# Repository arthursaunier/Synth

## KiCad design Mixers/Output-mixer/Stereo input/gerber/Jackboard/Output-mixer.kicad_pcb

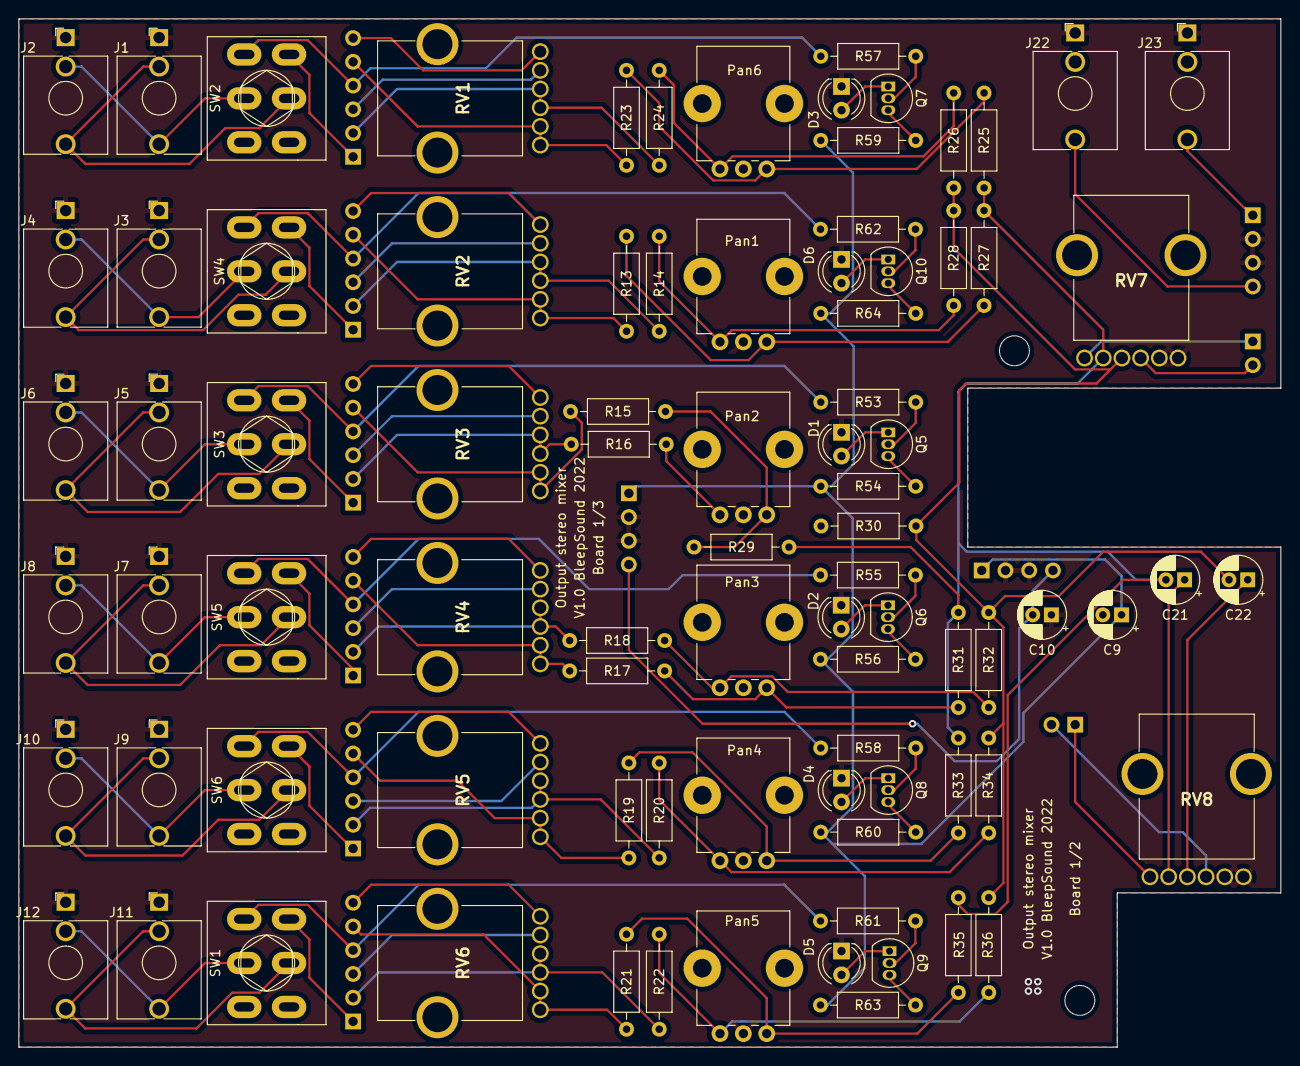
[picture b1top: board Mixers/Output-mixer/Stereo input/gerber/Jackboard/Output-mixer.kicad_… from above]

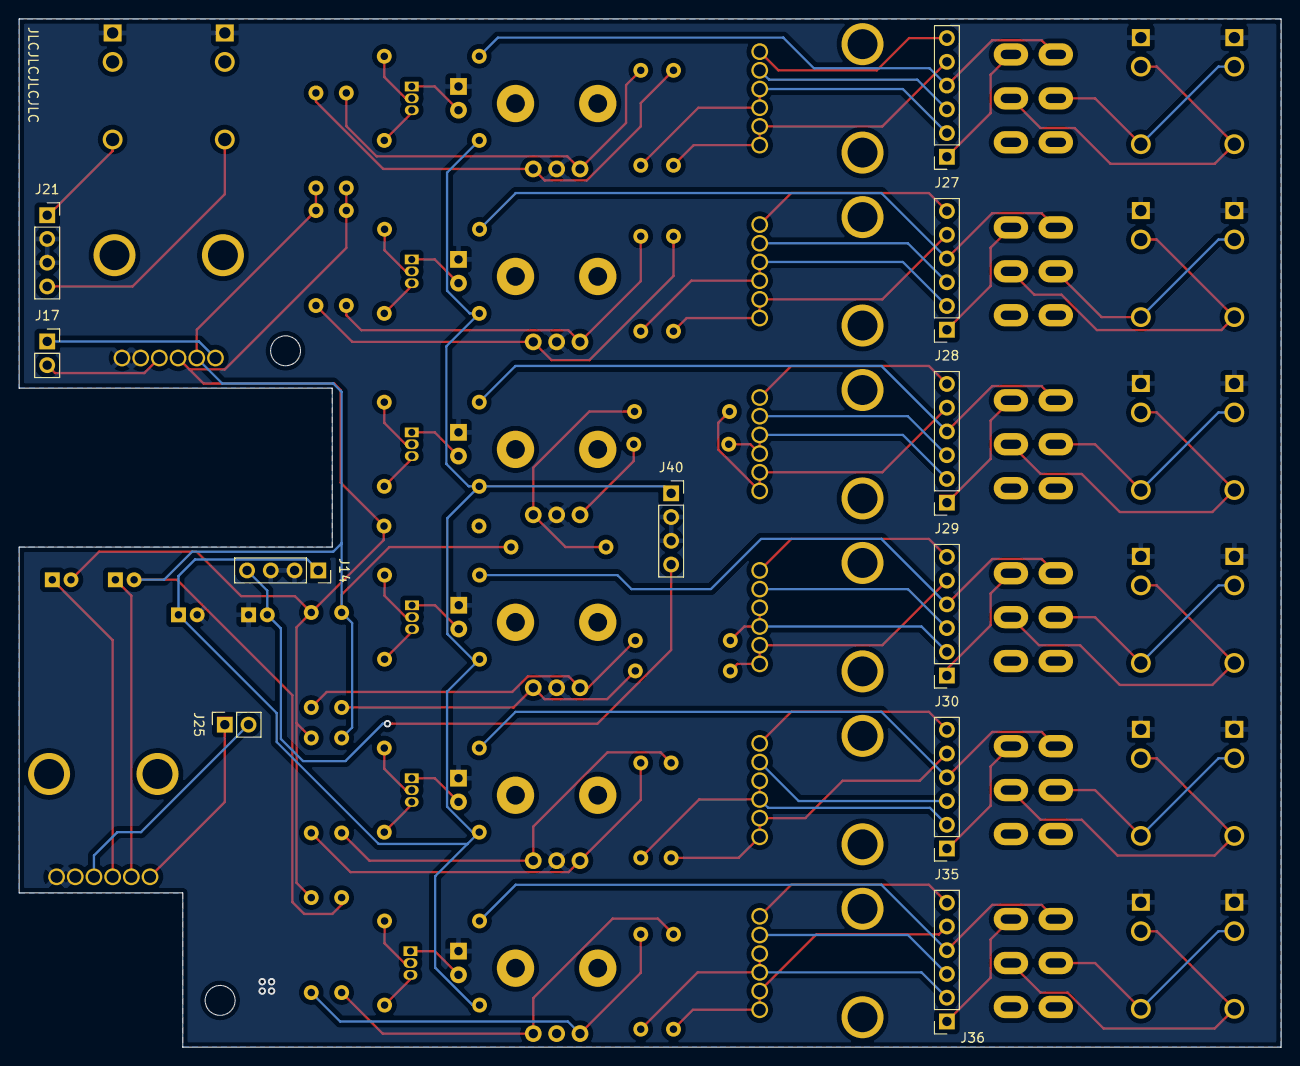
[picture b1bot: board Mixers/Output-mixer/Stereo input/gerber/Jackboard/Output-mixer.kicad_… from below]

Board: 2 copper layers, 135.0 x 110.0 mm, 99 parts (11 on the bottom side), 91 nets.

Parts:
C9, C10: 10µ; CP_Radial_D5.0mm_P2.00mm
C21, C22: 1µF; CP_Radial_D5.0mm_P2.00mm
D1, D2, D3, D4, D5, D6: Signal; LED_D4.0mm
H5, H7: SpacerHoles; MountingHole_3.2mm_M3
J1, J2, J3, J4, J5, J6, J7, J8, J9, J10, J11, J12: In; Thonkiconn
J14, J40: Conn_01x04_Female; PinSocket_1x04_P2.54mm_Vertical
J17, J25: Conn_01x02_Female; PinSocket_1x02_P2.54mm_Vertical
J21: Jack 3.5 Out; PinSocket_1x04_P2.54mm_Vertical
J22: OutL; Thonkiconn
J23: OutR; Thonkiconn
J27, J28, J29, J30, J35, J36: Conn_01x06_Female; PinSocket_1x06_P2.54mm_Vertical
Pan1, Pan2, Pan3, Pan4, Pan5, Pan6: 50k; Pot-bourns-alpha
Q5, Q6, Q7, Q8, Q9, Q10: 2N3904; TO-92_Inline
R13, R14, R15, R16, R17, R18, R19, R20, R21, R22, R23, R24: 2k2; R_Axial_DIN0207_L6.3mm_D2.5mm_P10.16mm_Horizontal
R25, R26, R27, R28, R29, R30, R31, R32, R33, R34, R35, R36: 47k; R_Axial_DIN0207_L6.3mm_D2.5mm_P10.16mm_Horizontal
R53, R55, R57, R58, R61, R62: 100k; R_Axial_DIN0207_L6.3mm_D2.5mm_P10.16mm_Horizontal
R54, R56, R59, R60, R63, R64: 1k; R_Axial_DIN0207_L6.3mm_D2.5mm_P10.16mm_Horizontal
RV1, RV2, RV3, RV4, RV5, RV6, RV7, RV8: 50k; PTV1124420AA503
SW1, SW2, SW3, SW4, SW5, SW6: Mute; SW_DPDT_Toggle

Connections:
+12V: C9.1, J14.1, J40.1, R54.1, R56.1, R59.1, R60.1, R63.1, R64.1
-12V: C10.2, J14.4, J40.4
/AmpL: J17.1, RV7.2
/AmpR: J17.2, RV7.5
/Headphones Amp/HeadAmpL: J25.1, RV8.2
/Headphones Amp/HeadAmpR: J25.2, RV8.5
/OutL: J21.4, J22.T
/OutR: J21.1, J23.T
GND: C9.2, C10.1, D1.1 (K), D2.1 (K), D3.1 (K), D4.1 (K), D5.1 (K), D6.1 (K), J1.S, J2.S, J3.S, J4.S, J5.S, J6.S, J7.S, J8.S, J9.S, J10.S, J11.S, J12.S, J14.2, J14.3, J21.2, J21.3, J22.S, J23.S, J40.2, J40.3, Pan1.2, Pan2.2, Pan3.2, Pan4.2, Pan5.2, Pan6.2, RV7.3, RV7.6, RV8.3, RV8.6
L: C21.2, R25.2, R27.2, R29.2, R31.2, R33.2, R35.2, RV7.1
Left1_GOut: J27.3, RV1.6
Left1_In: J27.1, SW2.4 (A)
Left1_Out: J27.2, R24.2, RV1.4, RV1.5
Left2_GOut: J28.3, RV2.6
Left2_In: J28.1, SW4.4 (A)
Left2_Out: J28.2, R14.2, RV2.4, RV2.5
Left3_GOut: J29.3, RV3.6
Left3_In: J29.1, SW3.4 (A)
Left3_Out: J29.2, R16.2, RV3.4, RV3.5
Left4_GOut: J30.3, RV4.6
Left4_In: J30.1, SW5.4 (A)
Left4_Out: J30.2, R18.2, RV4.4, RV4.5
Left5_GOut: J35.3, RV5.6
Left5_In: J35.1, SW6.4 (A)
Left5_Out: J35.2, R20.2, RV5.4, RV5.5
Left6_GOut: J36.3, RV6.6
Left6_In: J36.1, SW1.4 (A)
Left6_Out: J36.2, R22.2, RV6.4, RV6.5
unnamed: C21.1, RV8.1
unnamed: C22.1, RV8.4
unnamed: D1.2 (A), Q5.1 (E)
unnamed: D2.2 (A), Q6.1 (E)
unnamed: D3.2 (A), Q7.1 (E)
unnamed: D4.2 (A), Q8.1 (E)
unnamed: D5.2 (A), Q9.1 (E)
unnamed: D6.2 (A), Q10.1 (E)
unnamed: J1.T, J2.TN, SW2.2 (B)
unnamed: J1.TN, J2.T, SW2.5 (B)
unnamed: J3.T, J4.TN, SW4.2 (B)
unnamed: J3.TN, J4.T, SW4.5 (B)
unnamed: J5.T, J6.TN, SW3.2 (B)
unnamed: J5.TN, J6.T, SW3.5 (B)
unnamed: J7.T, J8.TN, SW5.2 (B)
unnamed: J7.TN, J8.T, SW5.5 (B)
unnamed: J9.TN, J10.T, SW6.5 (B)
unnamed: J9.T, J10.TN, SW6.2 (B)
unnamed: J11.T, J12.TN, SW1.2 (B)
unnamed: J11.TN, J12.T, SW1.5 (B)
unnamed: Pan1.1, R13.2, R27.1
unnamed: Pan1.3, R14.1, R28.2
unnamed: Pan2.1, R15.2, R29.1
unnamed: Pan2.3, R16.1, R30.2
unnamed: Pan3.1, R17.2, R31.1
unnamed: Pan3.3, R18.1, R32.2
unnamed: Pan4.1, R19.2, R33.1
unnamed: Pan4.3, R20.1, R34.2
unnamed: Pan5.1, R21.2, R35.1
unnamed: Pan5.3, R22.1, R36.2
unnamed: Pan6.1, R23.2, R25.1
unnamed: Pan6.3, R24.1, R26.2
unnamed: Q5.2 (B), R53.2
unnamed: Q5.3 (C), R54.2
unnamed: Q6.2 (B), R55.2
unnamed: Q6.3 (C), R56.2
unnamed: Q7.2 (B), R57.2
unnamed: Q7.3 (C), R59.2
unnamed: Q8.2 (B), R58.2
unnamed: Q8.3 (C), R60.2
unnamed: Q9.2 (B), R61.2
unnamed: Q9.3 (C), R63.2
unnamed: Q10.2 (B), R62.2
unnamed: Q10.3 (C), R64.2
R: C22.2, R26.1, R28.1, R30.1, R32.1, R34.1, R36.1, RV7.4
Right1_GOut: J27.6, RV1.3
Right1_In: J27.4, R57.1, SW2.1 (A)
Right1_Out: J27.5, R23.1, RV1.1, RV1.2
Right2_GOut: J28.6, RV2.3
Right2_In: J28.4, R62.1, SW4.1 (A)
Right2_Out: J28.5, R13.1, RV2.1, RV2.2
Right3_GOut: J29.6, RV3.3
Right3_In: J29.4, R53.1, SW3.1 (A)
Right3_Out: J29.5, R15.1, RV3.1, RV3.2
Right4_GOut: J30.6, RV4.3
Right4_In: J30.4, R55.1, SW5.1 (A)
Right4_Out: J30.5, R17.1, RV4.1, RV4.2
Right5_GOut: J35.6, RV5.3
Right5_In: J35.4, R58.1, SW6.1 (A)
Right5_Out: J35.5, R19.1, RV5.1, RV5.2
Right6_GOut: J36.6, RV6.3
Right6_In: J36.4, R61.1, SW1.1 (A)
Right6_Out: J36.5, R21.1, RV6.1, RV6.2

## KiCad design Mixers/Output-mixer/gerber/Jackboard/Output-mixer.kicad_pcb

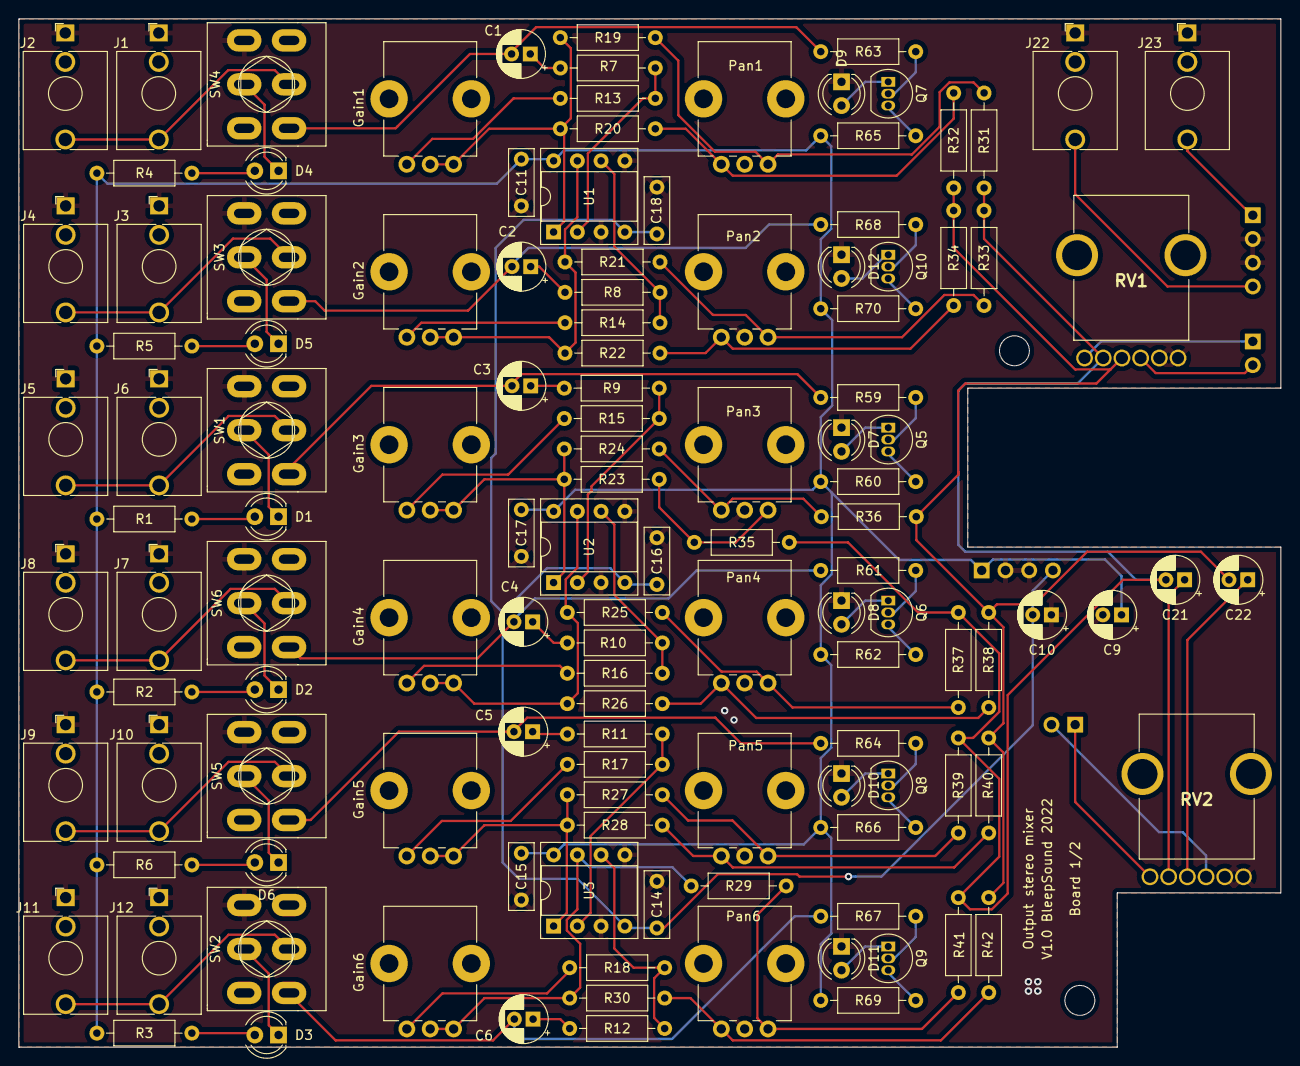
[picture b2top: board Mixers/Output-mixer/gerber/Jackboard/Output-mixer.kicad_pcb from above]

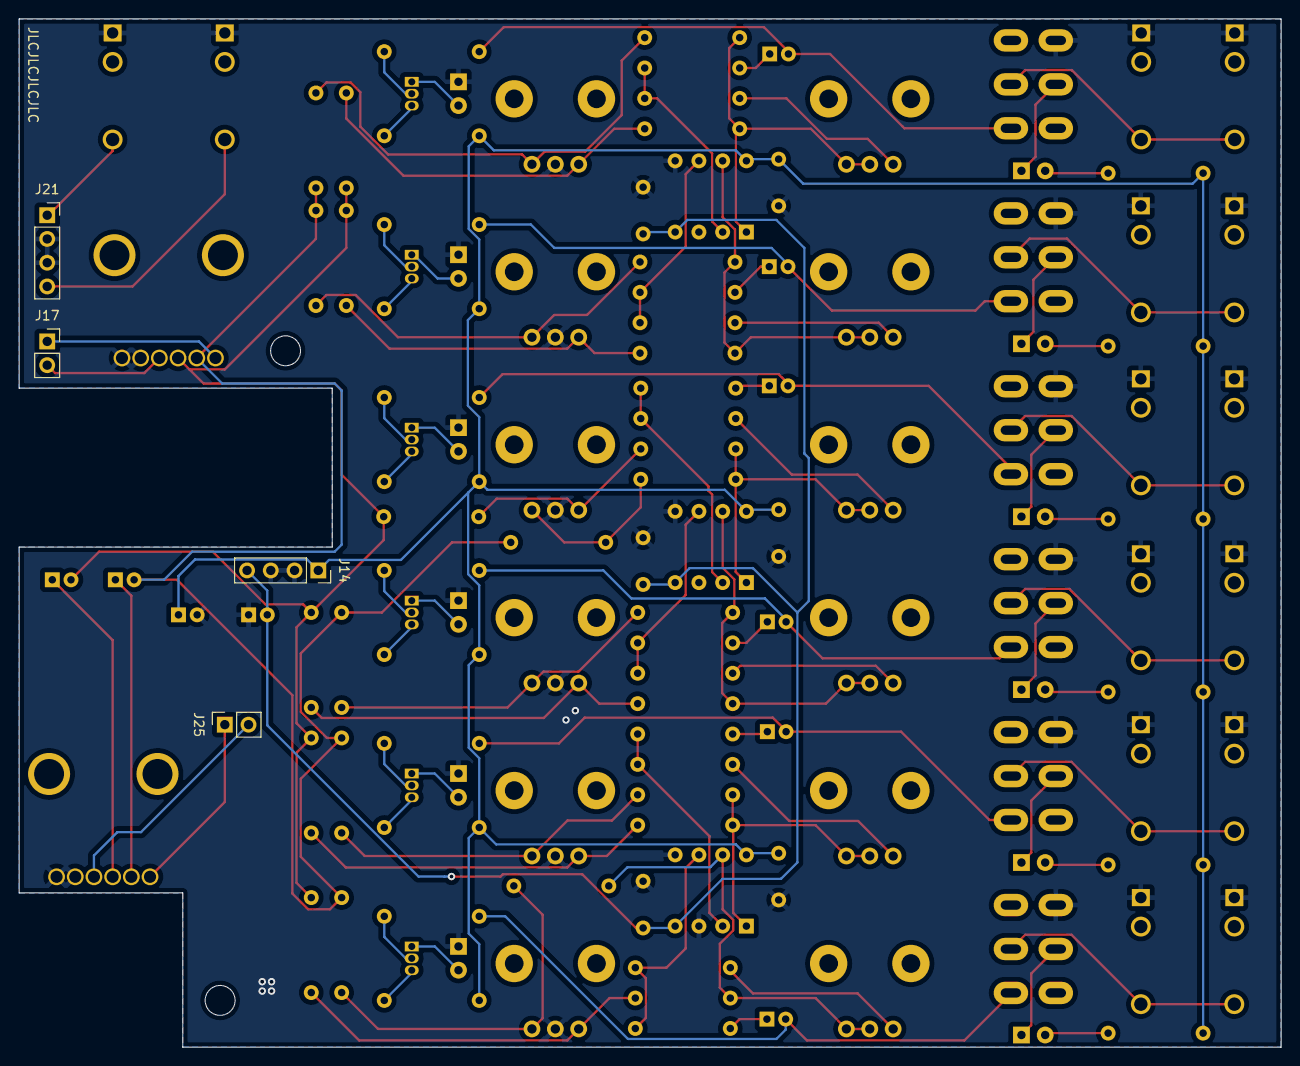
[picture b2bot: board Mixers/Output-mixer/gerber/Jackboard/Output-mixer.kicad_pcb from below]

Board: 2 copper layers, 135.0 x 110.0 mm, 131 parts (4 on the bottom side), 91 nets.

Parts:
C1, C2, C3, C4, C5, C6: .1µF; CP_Radial_D5.0mm_P2.00mm
C9, C10: 10µ; CP_Radial_D5.0mm_P2.00mm
C11, C14, C15, C16, C17, C18: 100nF; C_Disc_D7.0mm_W2.5mm_P5.00mm
C21, C22: 1µF; CP_Radial_D5.0mm_P2.00mm
D1, D2, D3, D4, D5, D6: LED-mute; LED_D4.0mm
D7, D8, D9, D10, D11, D12: Signal; LED_D4.0mm
Gain1, Gain2, Gain3, Gain4, Gain5, Gain6: 500k; Pot-bourns-alpha
H5, H7: SpacerHoles; MountingHole_3.2mm_M3
J1, J2, J3, J4, J5, J6, J7, J8, J9, J10, J11, J12: In; Thonkiconn
J14: Conn_01x04_Female; PinSocket_1x04_P2.54mm_Vertical
J17, J25: Conn_01x02_Female; PinSocket_1x02_P2.54mm_Vertical
J21: Jack 3.5 Out; PinSocket_1x04_P2.54mm_Vertical
J22: OutL; Thonkiconn
J23: OutR; Thonkiconn
Pan1, Pan2, Pan3, Pan4, Pan5, Pan6: 50k; Pot-bourns-alpha
Q5, Q6, Q7, Q8, Q9, Q10: 2N3904; TO-92_Inline
R1, R2, R3, R4, R5, R6: 2.2k; R_Axial_DIN0207_L6.3mm_D2.5mm_P10.16mm_Horizontal
R7, R8, R9, R10, R11, R12, R59, R61, R63, R64, R67, R68: 100k; R_Axial_DIN0207_L6.3mm_D2.5mm_P10.16mm_Horizontal
R13, R14, R15, R16, R17, R18: 10k; R_Axial_DIN0207_L6.3mm_D2.5mm_P10.16mm_Horizontal
R19, R20, R21, R22, R23, R24, R25, R26, R27, R28, R29, R30: 2k2; R_Axial_DIN0207_L6.3mm_D2.5mm_P10.16mm_Horizontal
R31, R32, R33, R34, R35, R36, R37, R38, R39, R40, R41, R42: 47k; R_Axial_DIN0207_L6.3mm_D2.5mm_P10.16mm_Horizontal
R60, R62, R65, R66, R69, R70: 1k; R_Axial_DIN0207_L6.3mm_D2.5mm_P10.16mm_Horizontal
RV1, RV2: 50k; PTV1124420AA503
SW1, SW2, SW3, SW4, SW5, SW6: Mute; SW_DPDT_Toggle
U1, U2, U3: TL072; DIP-8_W7.62mm_Socket

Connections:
+12V: C9.1, C11.1, C15.1, C17.1, J14.1, R1.1, R2.1, R3.1, R4.1, R5.1, R6.1, R60.1, R62.1, R65.1, R66.1, R69.1, R70.1, U1.8 (V+), U2.8 (V+), U3.8 (V+)
-12V: C10.2, C14.2, C16.2, C18.2, J14.4, U1.4 (V-), U2.4 (V-), U3.4 (V-)
/AmpL: J17.1, RV1.2
/AmpR: J17.2, RV1.5
/Headphones Amp/HeadAmpL: J25.1, RV2.2
/Headphones Amp/HeadAmpR: J25.2, RV2.5
/OutL: J21.4, J22.T
/OutR: J21.1, J23.T
GND: C9.2, C10.1, C11.2, C14.1, C15.2, C16.1, C17.2, C18.1, D7.1 (K), D8.1 (K), D9.1 (K), D10.1 (K), D11.1 (K), D12.1 (K), J1.S, J2.S, J3.S, J4.S, J5.S, J6.S, J7.S, J8.S, J9.S, J10.S, J11.S, J12.S, J14.2, J14.3, J21.2, J21.3, J22.S, J23.S, Pan1.2, Pan2.2, Pan3.2, Pan4.2, Pan5.2, Pan6.2, RV1.3, RV1.6, RV2.3, RV2.6, SW1.1 (A), SW2.1 (A), SW3.1 (A), SW4.1 (A), SW5.1 (A), SW6.1 (A), U1.3 (+), U1.5 (+), U2.3 (+), U2.5 (+), U3.3 (+), U3.5 (+)
In1: C1.2, R63.1, SW4.6 (C)
In2: C2.2, R68.1, SW3.6 (C)
In3: C3.2, R59.1, SW1.6 (C)
In4: C4.2, R61.1, SW6.6 (C)
In5: C5.2, R64.1, SW5.6 (C)
In6: C6.2, R67.1, SW2.6 (C)
L: C21.2, R31.2, R33.2, R35.2, R37.2, R39.2, R41.2, RV1.1
unnamed: C1.1, R7.2
unnamed: C2.1, R8.2
unnamed: C3.1, R9.2
unnamed: C4.1, R10.2
unnamed: C5.1, R11.2
unnamed: C6.1, R12.2
unnamed: C21.1, RV2.1
unnamed: C22.1, RV2.4
unnamed: D1.1 (K), SW1.2 (B)
unnamed: D1.2 (A), R1.2
unnamed: D2.1 (K), SW6.2 (B)
unnamed: D2.2 (A), R2.2
unnamed: D3.1 (K), SW2.2 (B)
unnamed: D3.2 (A), R3.2
unnamed: D4.1 (K), SW4.2 (B)
unnamed: D4.2 (A), R4.2
unnamed: D5.1 (K), SW3.2 (B)
unnamed: D5.2 (A), R5.2
unnamed: D6.1 (K), SW5.2 (B)
unnamed: D6.2 (A), R6.2
unnamed: D7.2 (A), Q5.1 (E)
unnamed: D8.2 (A), Q6.1 (E)
unnamed: D9.2 (A), Q7.1 (E)
unnamed: D10.2 (A), Q8.1 (E)
unnamed: D11.2 (A), Q9.1 (E)
unnamed: D12.2 (A), Q10.1 (E)
unnamed: Gain1.1, Gain1.2, R19.1, R20.2, U1.1
unnamed: Gain1.3, R13.1
unnamed: Gain2.1, Gain2.2, R21.1, R22.2, U1.7
unnamed: Gain2.3, R14.1
unnamed: Gain3.1, Gain3.2, R23.1, R24.2, U2.1
unnamed: Gain3.3, R15.1
unnamed: Gain4.1, Gain4.2, R25.1, R26.2, U2.7
unnamed: Gain4.3, R16.1
unnamed: Gain5.1, Gain5.2, R27.1, R28.2, U3.1
unnamed: Gain5.3, R17.1
unnamed: Gain6.1, Gain6.2, R29.1, R30.2, U3.7
unnamed: Gain6.3, R18.1
unnamed: J1.T, J2.T, SW4.5 (B)
unnamed: J3.T, J4.T, SW3.5 (B)
unnamed: J5.T, J6.T, SW1.5 (B)
unnamed: J7.T, J8.T, SW6.5 (B)
unnamed: J9.T, J10.T, SW5.5 (B)
unnamed: J11.T, J12.T, SW2.5 (B)
unnamed: Pan1.1, R19.2, R31.1
unnamed: Pan1.3, R20.1, R32.2
unnamed: Pan2.1, R21.2, R33.1
unnamed: Pan2.3, R22.1, R34.2
unnamed: Pan3.1, R23.2, R35.1
unnamed: Pan3.3, R24.1, R36.2
unnamed: Pan4.1, R25.2, R37.1
unnamed: Pan4.3, R26.1, R38.2
unnamed: Pan5.1, R27.2, R39.1
unnamed: Pan5.3, R28.1, R40.2
unnamed: Pan6.1, R29.2, R41.1
unnamed: Pan6.3, R30.1, R42.2
unnamed: Q5.2 (B), R59.2
unnamed: Q5.3 (C), R60.2
unnamed: Q6.2 (B), R61.2
unnamed: Q6.3 (C), R62.2
unnamed: Q7.2 (B), R63.2
unnamed: Q7.3 (C), R65.2
unnamed: Q8.2 (B), R64.2
unnamed: Q8.3 (C), R66.2
unnamed: Q9.2 (B), R67.2
unnamed: Q9.3 (C), R69.2
unnamed: Q10.2 (B), R68.2
unnamed: Q10.3 (C), R70.2
unnamed: R10.1, R16.2, U2.6 (-)
unnamed: R11.1, R17.2, U3.2 (-)
unnamed: R12.1, R18.2, U3.6 (-)
unnamed: R7.1, R13.2, U1.2 (-)
unnamed: R8.1, R14.2, U1.6 (-)
unnamed: R9.1, R15.2, U2.2 (-)
R: C22.2, R32.1, R34.1, R36.1, R38.1, R40.1, R42.1, RV1.4

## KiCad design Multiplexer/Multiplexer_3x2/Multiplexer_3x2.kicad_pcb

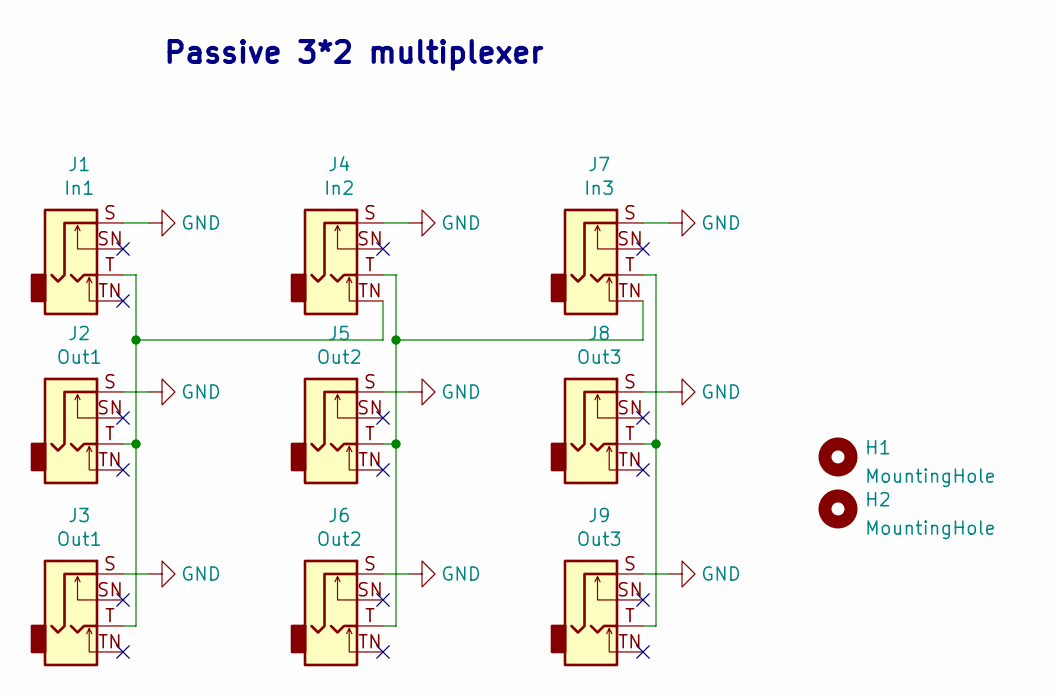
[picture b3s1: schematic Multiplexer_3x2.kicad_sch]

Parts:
H1, H2: MountingHole; Doepfer Mounting hole
J1: In1; Jack_3.5mm_QingPu_WQP-PJ398SM_Vertical_CircularHoles
J2, J3: Out1; Jack_3.5mm_QingPu_WQP-PJ398SM_Vertical_CircularHoles
J4: In2; Jack_3.5mm_QingPu_WQP-PJ398SM_Vertical_CircularHoles
J5, J6: Out2; Jack_3.5mm_QingPu_WQP-PJ398SM_Vertical_CircularHoles
J7: In3; Jack_3.5mm_QingPu_WQP-PJ398SM_Vertical_CircularHoles
J8, J9: Out3; Jack_3.5mm_QingPu_WQP-PJ398SM_Vertical_CircularHoles

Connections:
GND: J1.S, J2.S, J3.S, J4.S, J5.S, J6.S, J7.S, J8.S, J9.S
unnamed: J4.T, J5.T, J6.T, J7.TN
unnamed: J1.T, J2.T, J3.T, J4.TN
unnamed: J7.T, J8.T, J9.T

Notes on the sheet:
Passive 3*2 multiplexer

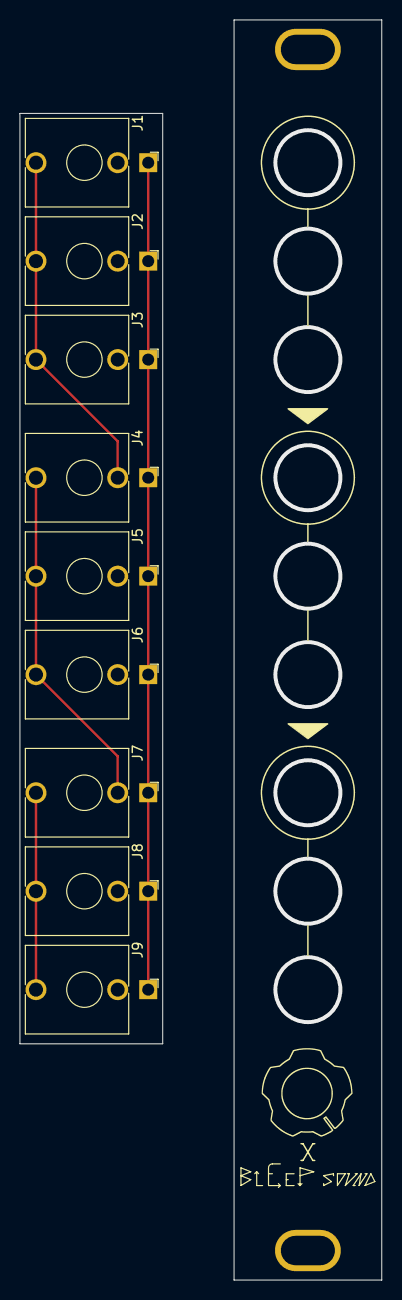
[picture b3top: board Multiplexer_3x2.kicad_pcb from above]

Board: 2 copper layers, 14.5 x 94.5 mm, 11 parts (0 on the bottom side), 4 nets.

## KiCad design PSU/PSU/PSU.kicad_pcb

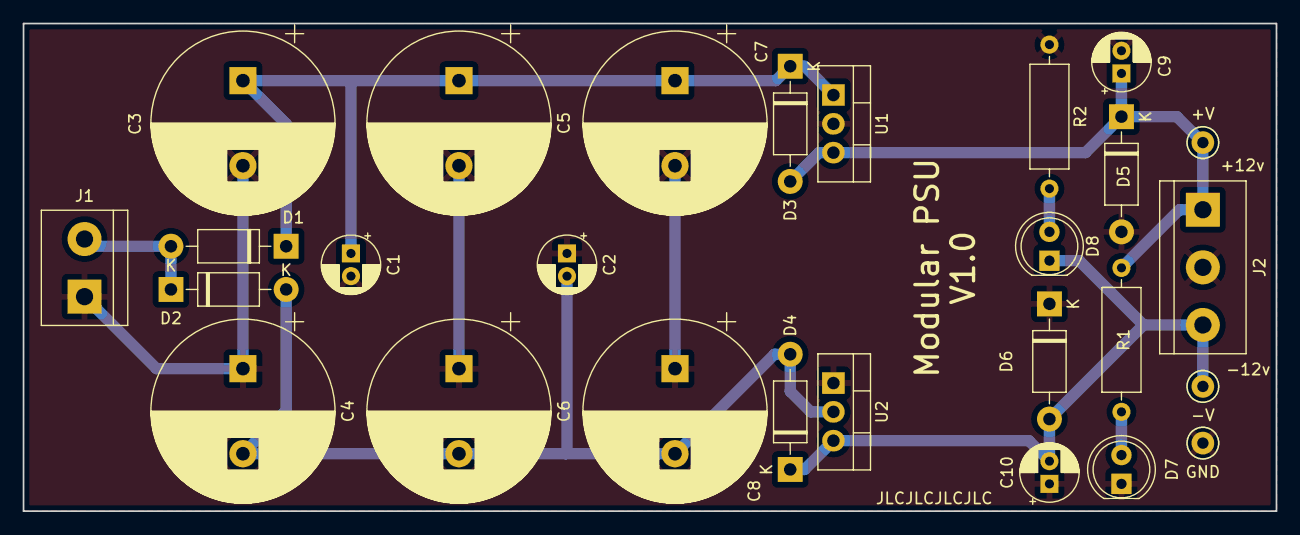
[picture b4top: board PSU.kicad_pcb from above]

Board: 2 copper layers, 110.5 x 43.0 mm, 27 parts (0 on the bottom side), 8 nets.

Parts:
C1, C2: 1µF; CP_Radial_D5.0mm_P2.00mm
C3, C4, C5, C6, C7, C8: 4700µF; CP_Radial_D16.0mm_P7.50mm
C9, C10: 100µF; CP_Radial_D5.0mm_P2.00mm
D1, D2, D3, D4, D5, D6: 1N4004; D_DO-41_SOD81_P10.16mm_Horizontal
D7, D8: LED; LED_D5.0mm_Clear
J1: Power_Input; TerminalBlock_bornier-2_P5.08mm
J2: Screw_Terminal_01x03; TerminalBlock_bornier-3_P5.08mm
R1, R2: 2.2k; R_Axial_DIN0309_L9.0mm_D3.2mm_P12.70mm_Horizontal
TP1: +V; TestPoint_Keystone_5000-5004_Miniature
TP2: GND; TestPoint_Keystone_5000-5004_Miniature
TP3: -V; TestPoint_Keystone_5000-5004_Miniature
U1: L7812; TO-220-3_Vertical
U2: L7912; TO-220-3_Vertical

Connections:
GND: C1.2, C2.1, C3.2, C4.1, C5.2, C6.1, C7.2, C8.1, C9.2, C10.1, D5.2 (A), D6.1 (K), D7.1 (K), J1.1, J2.2, R2.1, TP2.1, U1.2 (GND), U2.1 (GND)
unnamed: C1.1, C3.1, C5.1, C7.1, D1.1 (K), D3.1 (K), U1.1 (IN)
unnamed: C2.2, C4.2, C6.2, C8.2, D2.2 (A), D4.2 (A), U2.2 (VI)
unnamed: C9.1, D3.2 (A), D5.1 (K), J2.1, R1.2, TP1.1, U1.3 (OUT)
unnamed: C10.2, D4.1 (K), D6.2 (A), D8.1 (K), J2.3, TP3.1, U2.3 (VO)
unnamed: D1.2 (A), D2.1 (K), J1.2
unnamed: D7.2 (A), R1.1
unnamed: D8.2 (A), R2.2

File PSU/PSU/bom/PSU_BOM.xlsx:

References | Quantity | Value | Footprint | Specs | Link | Price/100 | Price
C3, C4, C5, C6, C7, C8 | 6 | 4700µF | CP_Radial_D16.0mm_P7.50mm | 4700µF, 25V | https://www.taydaelectronics.com/capacitors/electrolytic-cap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 | 0.6 | 3.5999999999999996
C1, C2 | 2 | 1µF | CP_Radial_D5.0mm_P2.00mm | 1µF, 50V | https://www.taydaelectronics.com/capacitors/electrolytic-cap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 | 0.02 | 0.04
C9, C10 | 2 | 100µF | CP_Radial_D5.0mm_P2.00mm | 100µF, 25V | https://www.taydaelectronics.com/capacitors/electrolytic-cap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 | 0.03 | 0.06
R1, R2 | 2 | 2.2k | R_Axial_DIN0309_L9.0mm_D3.2mm_P12.70mm_Horizontal | 1/4W metal film 1% resistor | https://www.taydaelectronics.com/resistors/1-4w-metal-film-r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 | 1.4999999999999999E-2 | 0.03
D1, D2, D3, D4, D5, D6 | 6 | 1N4004 | D_DO-41_SOD81_P10.16mm_Horizontal | 1N4004 | https://www.taydaelectronics.com/1n4004-diode-1a-400v.html | 0.02 | 0.12
D7, D8 | 2 | LED | LED_D5.0mm_Clear | 5mm round LED | https://www.taydaelectronics.com/leds/round-leds/5mm-leds.html | 0.03 | 0.06
U1 | 1 | L7812 | TO-220-3_Vertical | 12V TO-220 voltage regulator | https://www.taydaelectronics.com/l7812cv-lm7812-l7812-voltag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 | 0.33 | 0.33
U2 | 1 | L7912 | TO-220-3_Vertical | -12V TO-220 voltage regulator | https://www.taydaelectronics.com/l7912cv-lm7912-l7912-7912-v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 | 0.24 | 0.24
- | 2 | HeatSink | - | Heatsink for TO-220 | https://www.taydaelectronics.com/heat-sink-to-220-10-fins-1-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 | 0.24 | 0.48
J1 | 1 | Power_Input | TerminalBlock_bornier-2_P5.08mm | 2 poles, 5mm terminal block | https://www.taydaelectronics.com/dg126-screw-terminal-block-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 | 0.15 | 0.15
J2 | 1 | Screw_Terminal_01x03 | TerminalBlock_bornier-3_P5.08mm | 3 poles, 5mm terminal block | https://www.taydaelectronics.com/dg128-screw-terminal-block-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 | 0.15 | 0.15
 |  |  |  |  |  | Total | 5.26

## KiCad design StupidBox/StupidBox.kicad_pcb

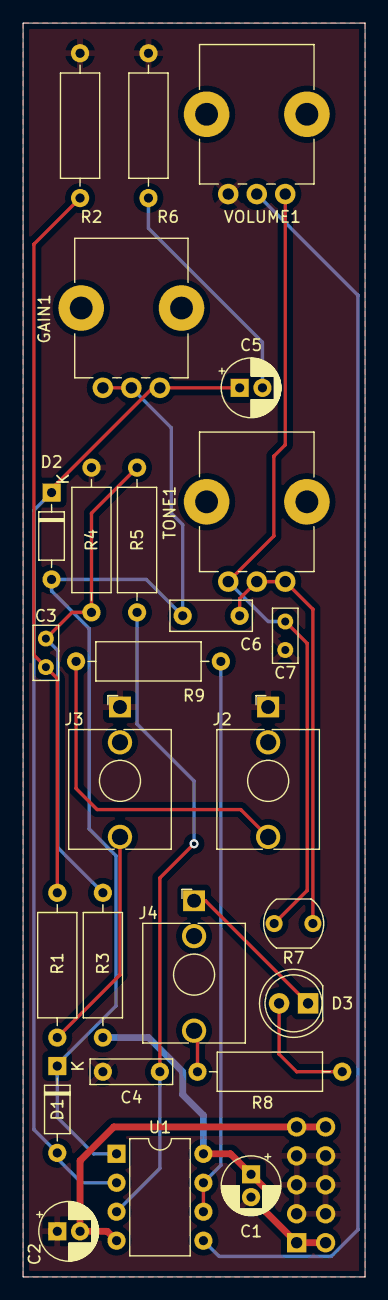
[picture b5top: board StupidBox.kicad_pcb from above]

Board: 2 copper layers, 30.0 x 110.0 mm, 27 parts (1 on the bottom side), 18 nets.

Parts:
C1, C2: 10µF; CP_Radial_D5.0mm_P2.00mm
C3, C7: 22nF; C_Rect_L4.6mm_W2.0mm_P2.50mm_MKS02_FKP02
C4: 500pF; C_Rect_L7.0mm_W2.0mm_P5.00mm
C5: 2.2µF; CP_Radial_D5.0mm_P2.00mm
C6: 100nF; C_Rect_L7.0mm_W2.5mm_P5.00mm
D1, D2: 1N914; D_DO-35_SOD27_P7.62mm_Horizontal
D3: LED; LED_D5.0mm
GAIN1: 100k; Potentiometer_Bourns_PTV09A-1_Single_Vertical
J1: POWER; PinHeader_2x05_P2.54mm_Vertical
J2: OUTPUT; Jack_3.5mm_QingPu_WQP-PJ398SM_Vertical_CircularHoles
J3: INPUT; Jack_3.5mm_QingPu_WQP-PJ398SM_Vertical_CircularHoles
J4: CV TONE; Jack_3.5mm_QingPu_WQP-PJ398SM_Vertical_CircularHoles
R1: 22k; R_Axial_DIN0309_L9.0mm_D3.2mm_P12.70mm_Horizontal
R2, R8: 2.2k; R_Axial_DIN0309_L9.0mm_D3.2mm_P12.70mm_Horizontal
R3: 150k; R_Axial_DIN0309_L9.0mm_D3.2mm_P12.70mm_Horizontal
R4, R5: 100k; R_Axial_DIN0309_L9.0mm_D3.2mm_P12.70mm_Horizontal
R6: 470; R_Axial_DIN0309_L9.0mm_D3.2mm_P12.70mm_Horizontal
R7: R_PHOTO; R_LDR_5.1x4.3mm_P3.4mm_Vertical
R9: 1k; R_Axial_DIN0309_L9.0mm_D3.2mm_P12.70mm_Horizontal
TONE1: 10k; Potentiometer_Alps_RK09K_Single_Vertical
U1: TL072; DIP-8_W7.62mm
VOLUME1: 50k; Potentiometer_Alps_RK09K_Single_Vertical

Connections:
+12V: C1.1, J1.1, J1.2, R3.1, U1.8 (V+)
-12V: C2.2, J1.9, J1.10, U1.4 (V-)
GND: C1.2, C2.1, C4.2, C7.2, J1.3, J1.4, J1.5, J1.6, J1.7, J1.8, J2.S, J3.S, R2.2, R4.2, R6.2, VOLUME1.3
INPUT: J3.T, R1.1
unnamed: C3.1, R3.2, R4.1, R5.1
unnamed: C3.2, R1.2, R2.1
unnamed: C4.1, R5.2, U1.3 (+)
unnamed: C5.1, D1.2 (A), D2.1 (K), GAIN1.1, U1.2 (-)
unnamed: C5.2, R6.1
unnamed: C6.1, R7.1, TONE1.1, TONE1.2
unnamed: C6.2, D1.1 (K), D2.2 (A), GAIN1.2, GAIN1.3, U1.1
unnamed: C7.1, R7.2, TONE1.3, VOLUME1.1
unnamed: D3.1 (K), J4.S
unnamed: D3.2 (A), R8.1
unnamed: J4.T, R8.2
unnamed: R9.1, U1.6 (-), U1.7
unnamed: U1.5 (+), VOLUME1.2
OUTPUT: J2.T, R9.2
